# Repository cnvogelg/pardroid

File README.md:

The parbox project implements an external device attached to the
Amiga parallel port that allows to directly connect network or mass
storage devices.

Currently, devices based on Atmel's AVR8 controllers are supported on the
device side.

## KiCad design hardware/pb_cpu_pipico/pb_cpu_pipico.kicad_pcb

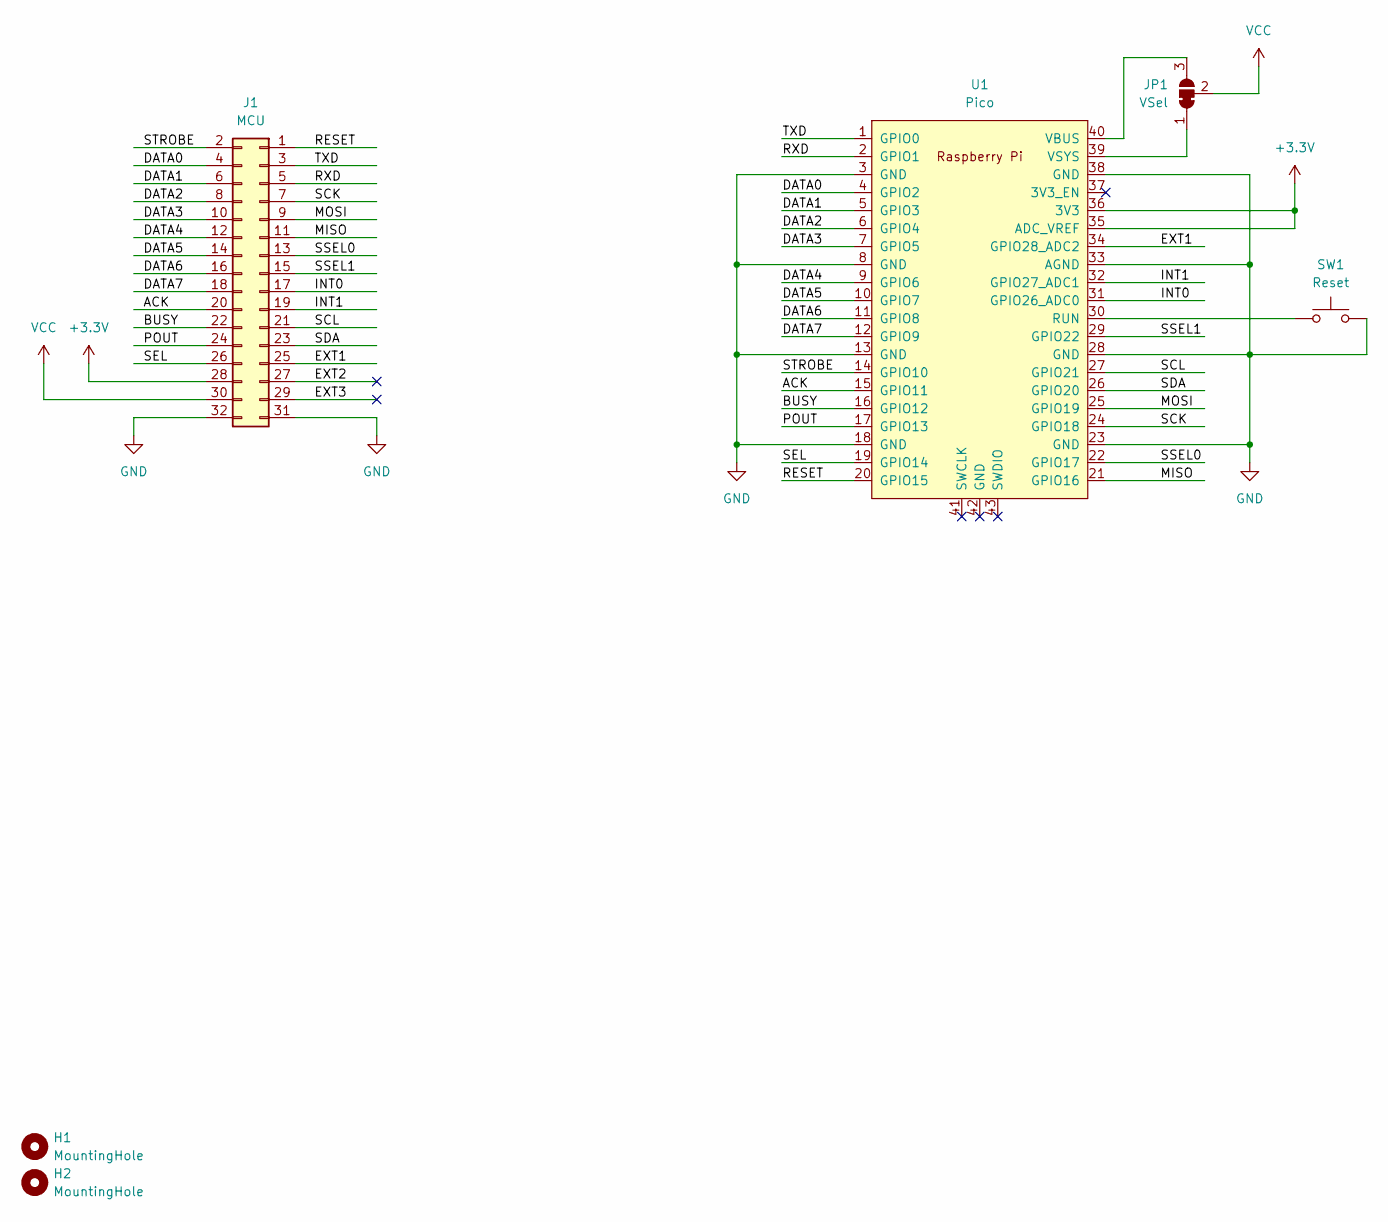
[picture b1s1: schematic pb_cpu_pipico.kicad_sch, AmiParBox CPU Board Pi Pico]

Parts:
H1, H2: MountingHole; MountingHole_3.2mm_M3_Pad
J1: MCU; PinHeader_2x16_P2.54mm_Vertical
JP1: VSel; SolderJumper-3_P1.3mm_Bridged2Bar12_Pad1.0x1.5mm
SW1: Reset; SW_PUSH_6mm
U1: Pico; RPi_Pico_SMD_TH

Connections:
+3V3: J1.28, U1.35 (ADC_VREF), U1.36 (3V3)
/ACK: J1.20, U1.15 (GPIO11)
/BUSY: J1.22, U1.16 (GPIO12)
/DATA0: J1.4, U1.4 (GPIO2)
/DATA1: J1.6, U1.5 (GPIO3)
/DATA2: J1.8, U1.6 (GPIO4)
/DATA3: J1.10, U1.7 (GPIO5)
/DATA4: J1.12, U1.9 (GPIO6)
/DATA5: J1.14, U1.10 (GPIO7)
/DATA6: J1.16, U1.11 (GPIO8)
/DATA7: J1.18, U1.12 (GPIO9)
/EXT1: J1.25, U1.34 (GPIO28_ADC2)
/EXT2: J1.27
/EXT3: J1.29
/INT0: J1.17, U1.31 (GPIO26_ADC0)
/INT1: J1.19, U1.32 (GPIO27_ADC1)
/MISO: J1.11, U1.21 (GPIO16)
/MOSI: J1.9, U1.25 (GPIO19)
/POUT: J1.24, U1.17 (GPIO13)
/RESET: J1.1, U1.20 (GPIO15)
/RXD: J1.5, U1.2 (GPIO1)
/SCK: J1.7, U1.24 (GPIO18)
/SCL: J1.21, U1.27 (GPIO21)
/SDA: J1.23, U1.26 (GPIO20)
/SEL: J1.26, U1.19 (GPIO14)
/SSEL0: J1.13, U1.22 (GPIO17)
/SSEL1: J1.15, U1.29 (GPIO22)
/STROBE: J1.2, U1.14 (GPIO10)
/TXD: J1.3, U1.1 (GPIO0)
GND: J1.31, J1.32, SW1.2, U1.3 (GND), U1.8 (GND), U1.13 (GND), U1.18 (GND), U1.23 (GND), U1.28 (GND), U1.33 (AGND), U1.38 (GND)
unnamed: JP1.1 (A), U1.39 (VSYS)
unnamed: JP1.3 (B), U1.40 (VBUS)
unnamed: SW1.1, U1.30 (RUN)
VCC: J1.30, JP1.2 (C)

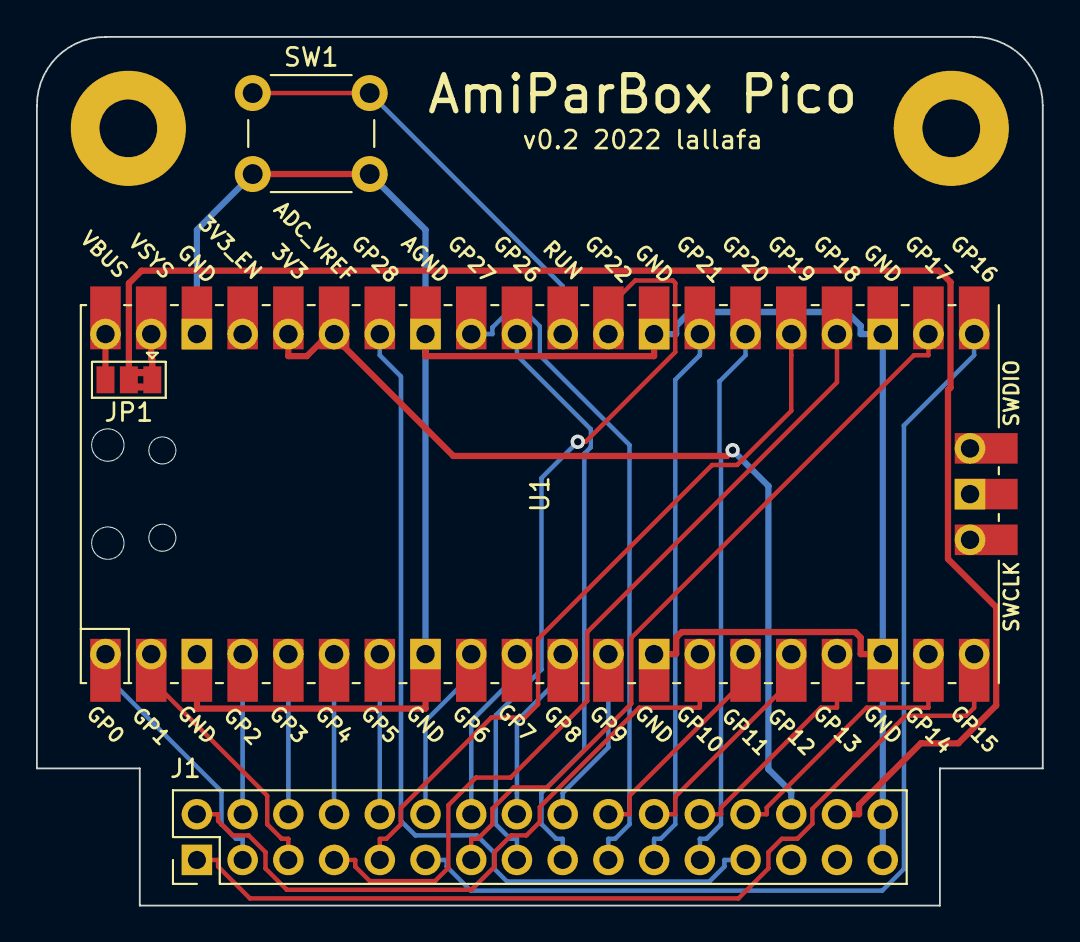
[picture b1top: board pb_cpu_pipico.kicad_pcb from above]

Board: 2 copper layers, 55.9 x 48.3 mm, 6 parts (0 on the bottom side), 32 nets.

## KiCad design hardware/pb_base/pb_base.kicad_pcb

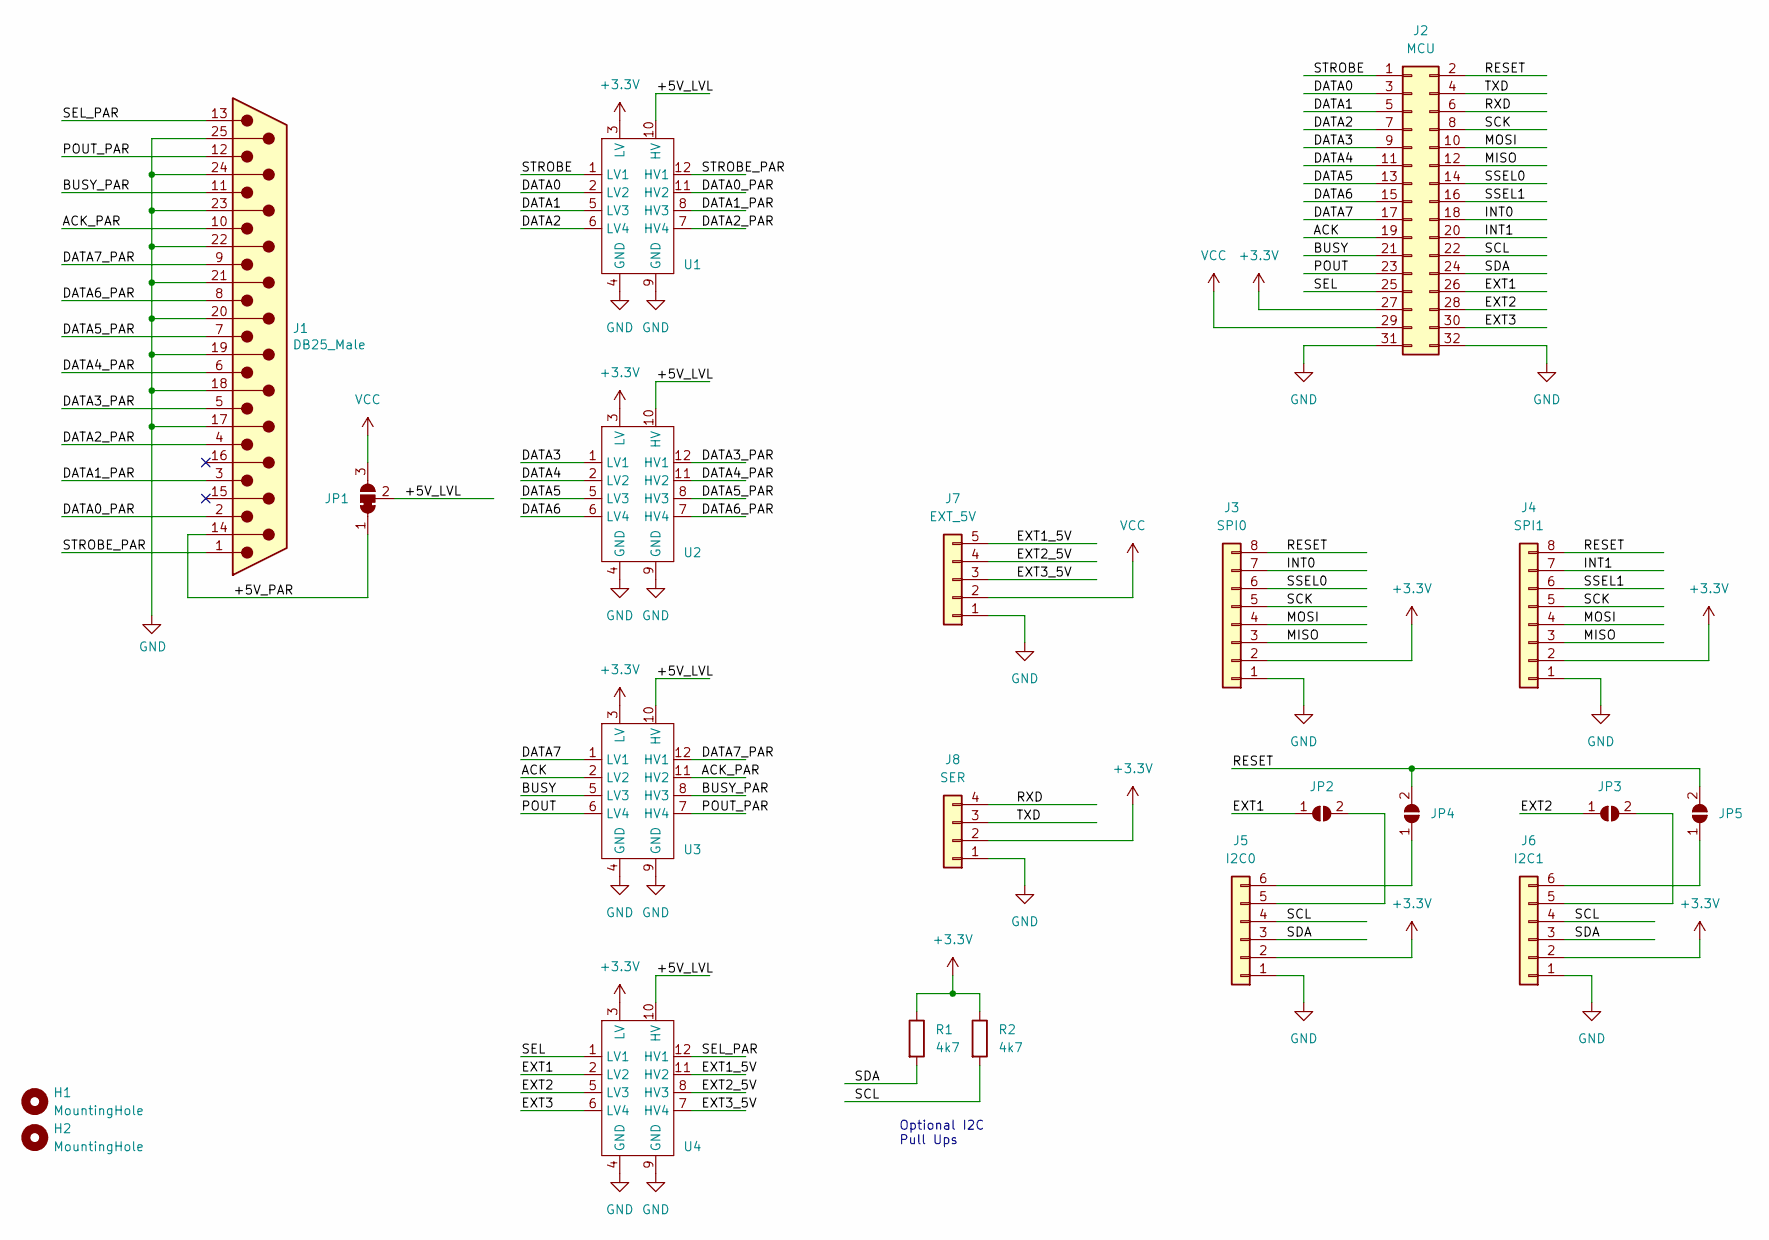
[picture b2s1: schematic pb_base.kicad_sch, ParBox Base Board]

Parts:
H1, H2: MountingHole; MountingHole_3.2mm_M3_Pad
J1: DB25_Male; DSUB-25_Male_Horizontal_P2.77x2.84mm_EdgePinOffset7.70mm_Ho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
J2: MCU; PinHeader_2x16_P2.54mm_Vertical
J3: SPI0; PinHeader_1x08_P2.54mm_Vertical
J4: SPI1; PinHeader_1x08_P2.54mm_Vertical
J5: I2C0; PinHeader_1x06_P2.54mm_Vertical
J6: I2C1; PinHeader_1x06_P2.54mm_Vertical
J7: EXT_5V; PinHeader_1x05_P2.54mm_Vertical
J8: SER; PinHeader_1x04_P2.54mm_Vertical
JP1: SolderJumper_3_Bridged12; PinHeader_1x03_P2.54mm_Vertical
JP2, JP3, JP4, JP5: SolderJumper_2_Open; PinHeader_1x02_P2.54mm_Vertical
R1, R2: 4k7; R_Axial_DIN0204_L3.6mm_D1.6mm_P5.08mm_Horizontal
U1, U2, U3, U4: LevelShifter_4; DIP-12_W10.16mm_LongPads

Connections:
+3V3: J2.27, J3.2, J4.2, J5.2, J6.2, J8.2, R1.1, R2.1, U1.3 (LV), U2.3 (LV), U3.3 (LV), U4.3 (LV)
/+5V_LVL: JP1.2 (C), U1.10 (HV), U2.10 (HV), U3.10 (HV), U4.10 (HV)
/+5V_PAR: J1.14, JP1.1 (A)
/ACK: J2.19, U3.2 (LV2)
/ACK_PAR: J1.10, U3.11 (HV2)
/BUSY: J2.21, U3.5 (LV3)
/BUSY_PAR: J1.11, U3.8 (HV3)
/DATA0: J2.3, U1.2 (LV2)
/DATA0_PAR: J1.2, U1.11 (HV2)
/DATA1: J2.5, U1.5 (LV3)
/DATA1_PAR: J1.3, U1.8 (HV3)
/DATA2: J2.7, U1.6 (LV4)
/DATA2_PAR: J1.4, U1.7 (HV4)
/DATA3: J2.9, U2.1 (LV1)
/DATA3_PAR: J1.5, U2.12 (HV1)
/DATA4: J2.11, U2.2 (LV2)
/DATA4_PAR: J1.6, U2.11 (HV2)
/DATA5: J2.13, U2.5 (LV3)
/DATA5_PAR: J1.7, U2.8 (HV3)
/DATA6: J2.15, U2.6 (LV4)
/DATA6_PAR: J1.8, U2.7 (HV4)
/DATA7: J2.17, U3.1 (LV1)
/DATA7_PAR: J1.9, U3.12 (HV1)
/EXT1: J2.26, JP2.1 (A), U4.2 (LV2)
/EXT1_5V: J7.5, U4.11 (HV2)
/EXT2: J2.28, JP3.1 (A), U4.5 (LV3)
/EXT2_5V: J7.4, U4.8 (HV3)
/EXT3: J2.30, U4.6 (LV4)
/EXT3_5V: J7.3, U4.7 (HV4)
/INT0: J2.18, J3.7
/INT1: J2.20, J4.7
/MISO: J2.12, J3.3, J4.3
/MOSI: J2.10, J3.4, J4.4
/POUT: J2.23, U3.6 (LV4)
/POUT_PAR: J1.12, U3.7 (HV4)
/RESET: J2.2, J3.8, J4.8, JP4.2 (B), JP5.2 (B)
/RXD: J2.6, J8.4
/SCK: J2.8, J3.5, J4.5
/SCL: J2.22, J5.4, J6.4, R2.2
/SDA: J2.24, J5.3, J6.3, R1.2
/SEL: J2.25, U4.1 (LV1)
/SEL_PAR: J1.13, U4.12 (HV1)
/SSEL0: J2.14, J3.6
/SSEL1: J2.16, J4.6
/STROBE: J2.1, U1.1 (LV1)
/STROBE_PAR: J1.1, U1.12 (HV1)
/TXD: J2.4, J8.3
GND: J1.17, J1.18, J1.19, J1.20, J1.21, J1.22, J1.23, J1.24, J1.25, J2.31, J2.32, J3.1, J4.1, J5.1, J6.1, J7.1, J8.1, U1.4 (GND), U1.9 (GND), U2.4 (GND), U2.9 (GND), U3.4 (GND), U3.9 (GND), U4.4 (GND), U4.9 (GND)
unnamed: J5.5, JP2.2 (B)
unnamed: J5.6, JP4.1 (A)
unnamed: J6.5, JP3.2 (B)
unnamed: J6.6, JP5.1 (A)
VCC: J2.29, J7.2, JP1.3 (B)

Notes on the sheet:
Optional I2C Pull Ups

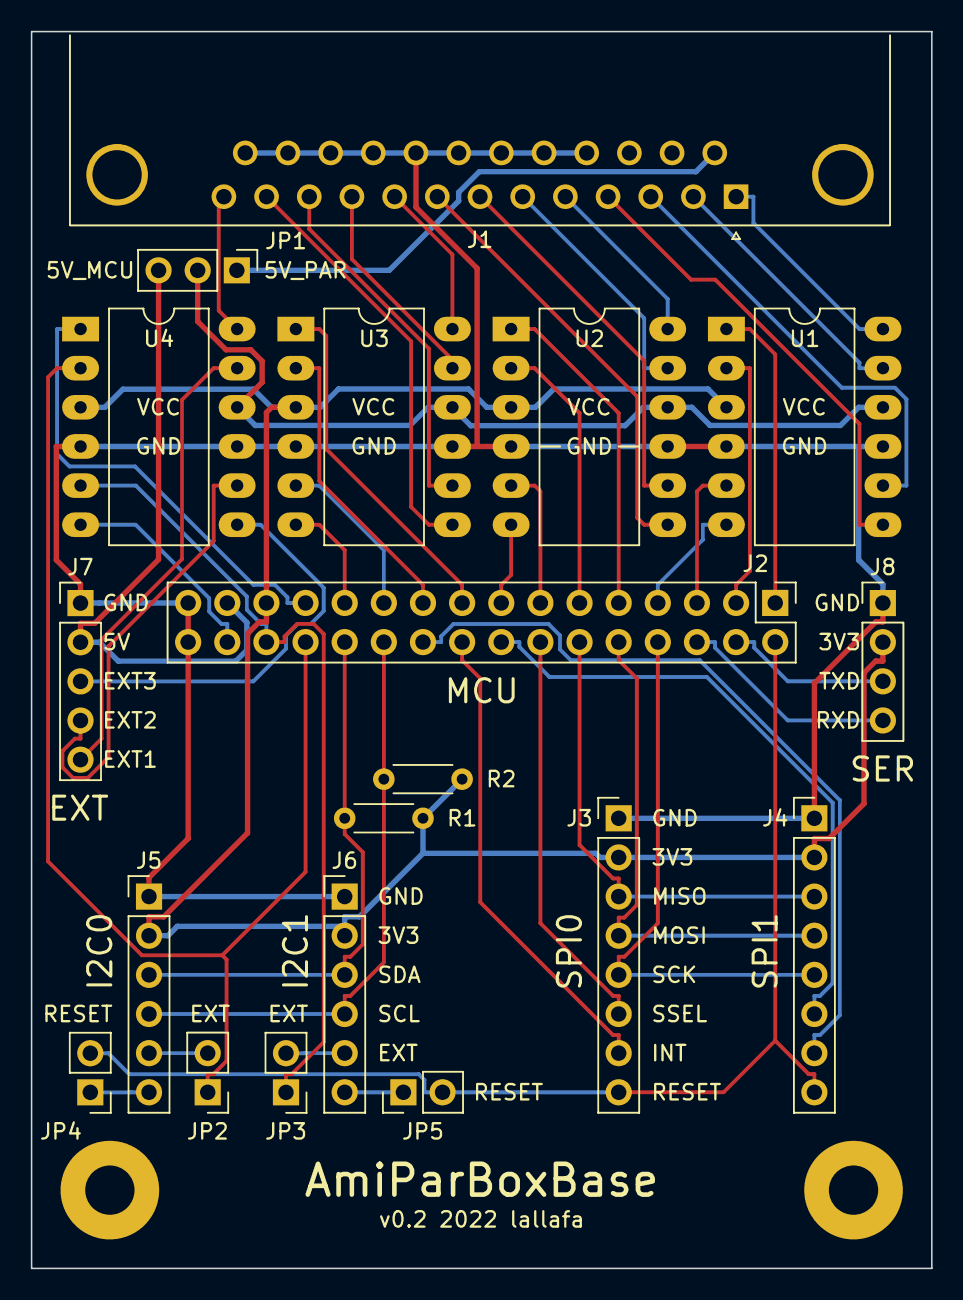
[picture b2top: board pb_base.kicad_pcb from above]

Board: 2 copper layers, 58.4 x 80.3 mm, 21 parts (0 on the bottom side), 53 nets.

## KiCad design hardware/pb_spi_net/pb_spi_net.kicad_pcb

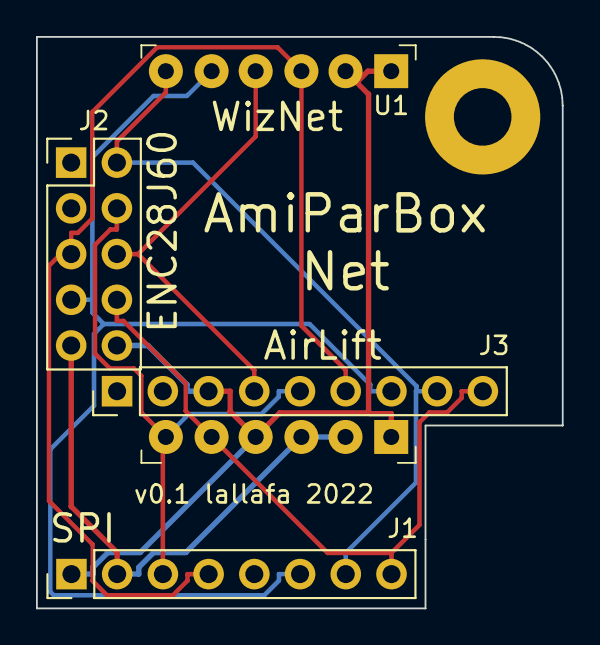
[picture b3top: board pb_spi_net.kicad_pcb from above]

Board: 2 copper layers, 29.2 x 31.8 mm, 5 parts (0 on the bottom side), 8 nets.

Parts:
H1: MountingHole; MountingHole_3.2mm_M3_Pad
J1: SPI; PinHeader_1x08_P2.54mm_Vertical
J2: ENC28J60 Module; PinHeader_2x05_P2.54mm_Vertical
J3: AirLift; PinHeader_1x09_P2.54mm_Vertical
U1: WIZ820IO; Mag_Jack_Module_WIZ820IO

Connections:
+3V3: J1.2, J2.9, U1.J2-2 (3V3D), U1.J2-3 (3V3D)
/INT: J1.7, J2.2, J3.8, U1.J1-6 (nINT)
/MISO: J1.3, J2.4, J3.5, U1.J2-6 (MISO)
/MOSI: J1.4, J2.5, J3.6, U1.J1-3 (MOSI)
/RESET: J1.8, J2.8, J3.9, U1.J2-5 (nRESET)
/SCLK: J2.6, J3.4, U1.J1-4 (SCLK)
/SSEL: J1.6, J2.7, J3.7, U1.J1-5 (nSS)
GND: J1.1, J2.10, J3.3, U1.J1-1 (GND), U1.J1-2 (GND), U1.J2-1 (GND), U1.J2-4 (PWDN)

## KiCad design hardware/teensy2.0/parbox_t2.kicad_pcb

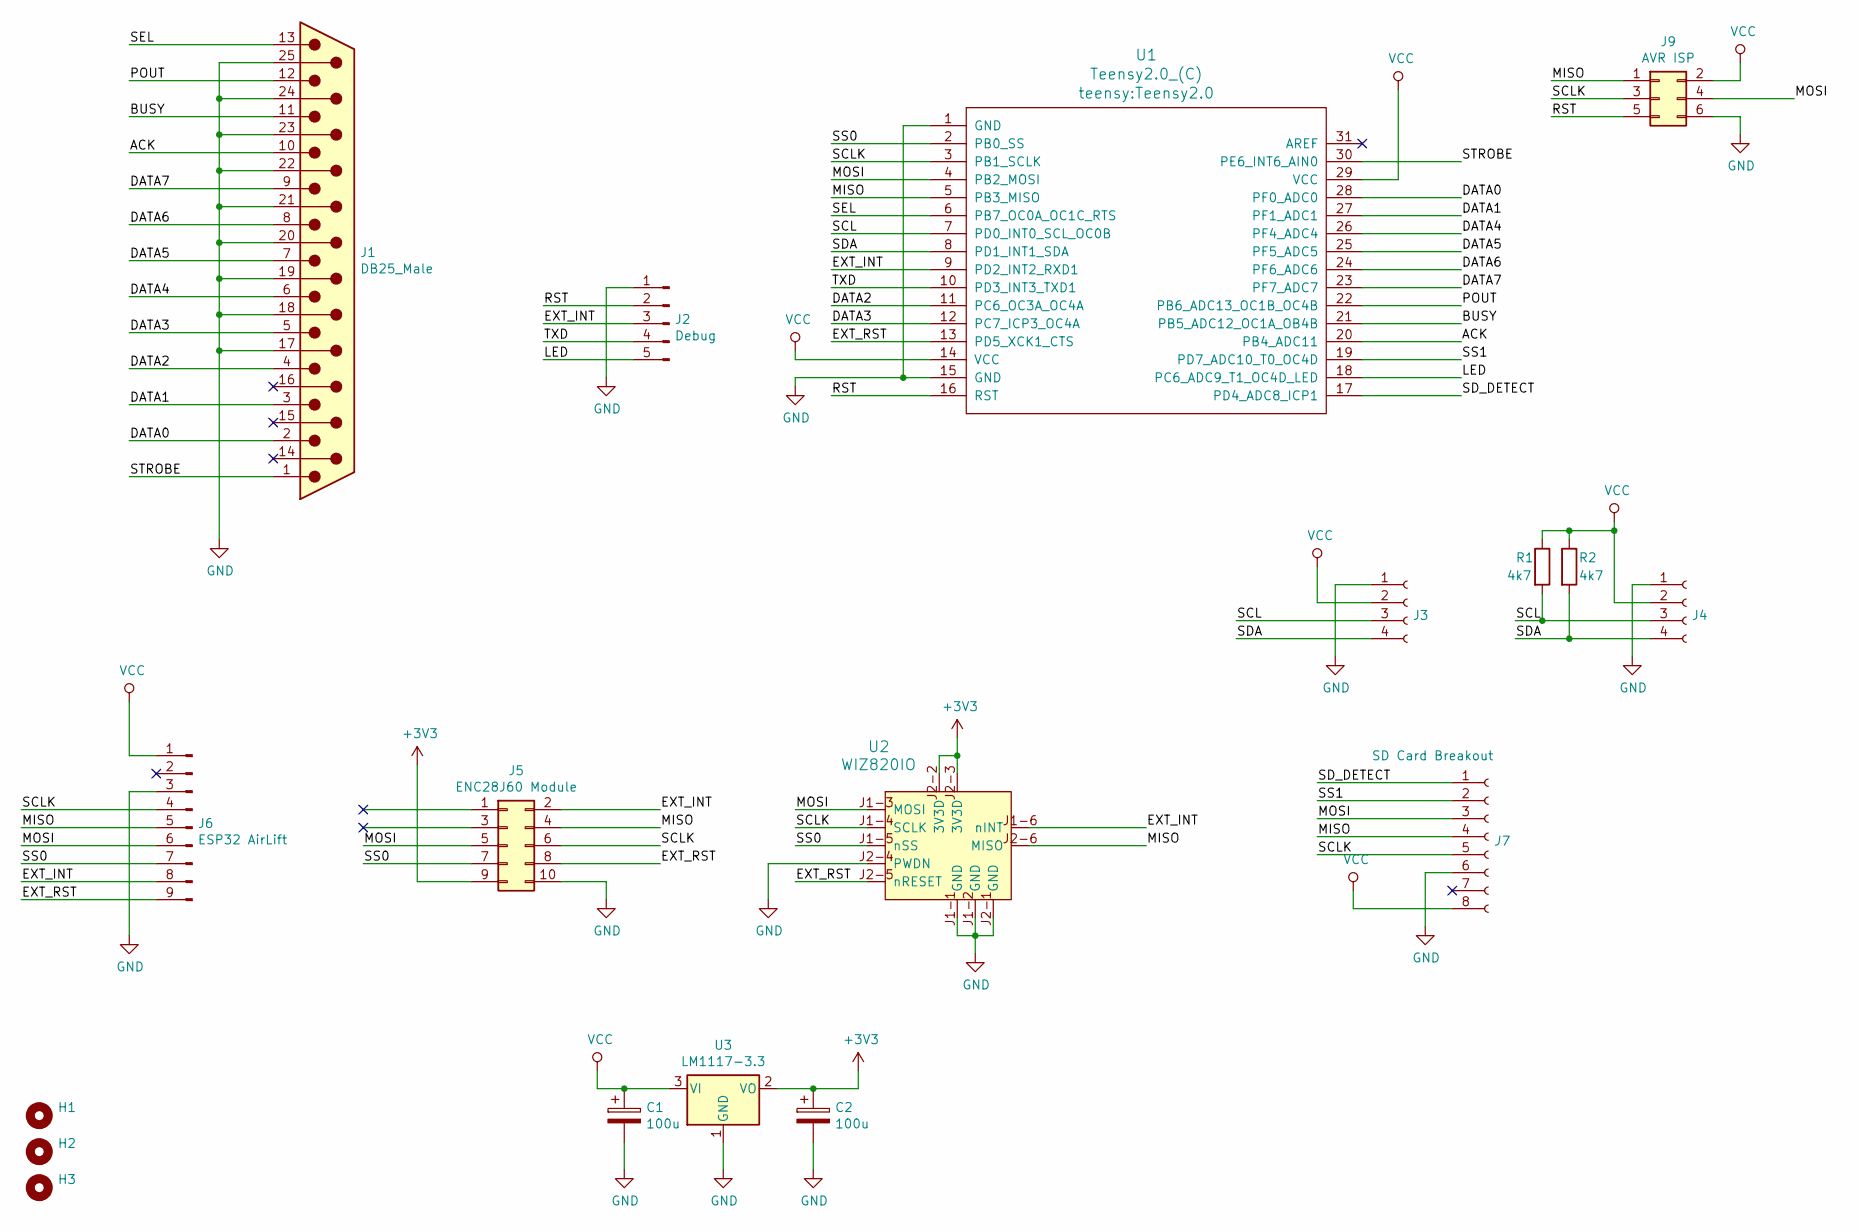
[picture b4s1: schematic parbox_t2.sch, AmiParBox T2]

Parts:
C1, C2: 100u; C_1210_3225Metric_Pad1.42x2.65mm_HandSolder
H1, H2, H3: MountingHole; MountingHole_2.7mm_M2.5_ISO14580_Pad
J1: DB25_Male; DSUB-25_Male_EdgeMount_P2.77mm
J2: Debug; PinHeader_1x05_P2.54mm_Vertical
J3: I2C OLED; PinHeader_1x04_P2.54mm_Vertical
J4: I2C Extra; PinHeader_1x04_P2.54mm_Vertical
J5: ENC28J60 Module; PinHeader_2x05_P2.54mm_Vertical
J6: ESP32 AirLift; PinHeader_1x09_P2.54mm_Vertical
J7: SD Card Breakout; PinHeader_1x08_P2.54mm_Vertical
J9: AVR ISP; PinHeader_2x03_P2.54mm_Vertical
R1, R2: 4k7; R_0805_2012Metric_Pad1.15x1.40mm_HandSolder
U1: Teensy2.0_(C); Teensy2.0
U2: WIZ820IO; Mag_Jack_Module_WIZ820IO; MPN WIZ820IO; Digi-Key_PN 1278-1015-ND
U3: LM1117-3.3; SOT-223-3_TabPin2

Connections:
+3V3: C2.1, J5.9, U2.J2-2 (3V3D), U2.J2-3 (3V3D), U3.2 (VO)
/ACK: J1.10, U1.20 (PB4_ADC11)
/BUSY: J1.11, U1.21 (PB5_ADC12_OC1A_OB4B)
/DATA0: J1.2, U1.28 (PF0_ADC0)
/DATA1: J1.3, U1.27 (PF1_ADC1)
/DATA2: J1.4, U1.11 (PC6_OC3A_OC4A)
/DATA3: J1.5, U1.12 (PC7_ICP3_OC4A)
/DATA4: J1.6, U1.26 (PF4_ADC4)
/DATA5: J1.7, U1.25 (PF5_ADC5)
/DATA6: J1.8, U1.24 (PF6_ADC6)
/DATA7: J1.9, U1.23 (PF7_ADC7)
/EXT_INT: J2.3, J5.2, J6.8, U1.9 (PD2_INT2_RXD1), U2.J1-6 (nINT)
/EXT_RST: J5.8, J6.9, U1.13 (PD5_XCK1_CTS), U2.J2-5 (nRESET)
/LED: J2.5, U1.18 (PC6_ADC9_T1_OC4D_LED)
/MISO: J5.4, J6.5, J7.4, J9.1, U1.5 (PB3_MISO), U2.J2-6 (MISO)
/MOSI: J5.5, J6.6, J7.3, J9.4, U1.4 (PB2_MOSI), U2.J1-3 (MOSI)
/POUT: J1.12, U1.22 (PB6_ADC13_OC1B_OC4B)
/RST: J2.2, J9.5, U1.16 (RST)
/SCL: J3.3, J4.3, R1.2, U1.7 (PD0_INT0_SCL_OC0B)
/SCLK: J5.6, J6.4, J7.5, J9.3, U1.3 (PB1_SCLK), U2.J1-4 (SCLK)
/SDA: J3.4, J4.4, R2.2, U1.8 (PD1_INT1_SDA)
/SD_DETECT: J7.1, U1.17 (PD4_ADC8_ICP1)
/SEL: J1.13, U1.6 (PB7_OC0A_OC1C_RTS)
/SS0: J5.7, J6.7, U1.2 (PB0_SS), U2.J1-5 (nSS)
/SS1: J7.2, U1.19 (PD7_ADC10_T0_OC4D)
/STROBE: J1.1, U1.30 (PE6_INT6_AIN0)
/TXD: J2.4, U1.10 (PD3_INT3_TXD1)
GND: C1.2, C2.2, J1.17, J1.18, J1.19, J1.20, J1.21, J1.22, J1.23, J1.24, J1.25, J2.1, J3.1, J4.1, J5.10, J6.3, J7.6, J9.6, U1.1 (GND), U1.15 (GND), U2.J1-1 (GND), U2.J1-2 (GND), U2.J2-1 (GND), U2.J2-4 (PWDN), U3.1 (GND)
VCC: C1.1, J3.2, J4.2, J6.1, J7.8, J9.2, R1.1, R2.1, U1.14 (VCC), U1.29 (VCC), U3.3 (VI)

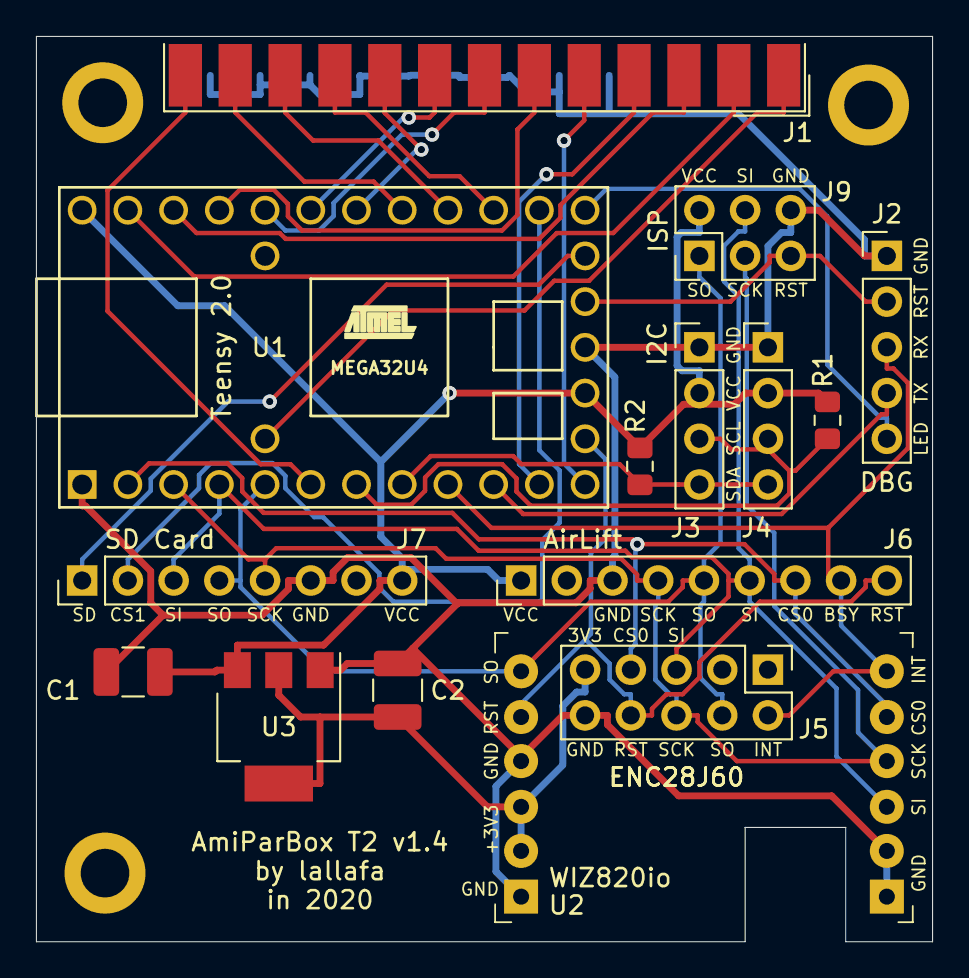
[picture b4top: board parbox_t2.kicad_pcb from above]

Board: 2 copper layers, 49.8 x 50.3 mm, 18 parts (0 on the bottom side), 29 nets.

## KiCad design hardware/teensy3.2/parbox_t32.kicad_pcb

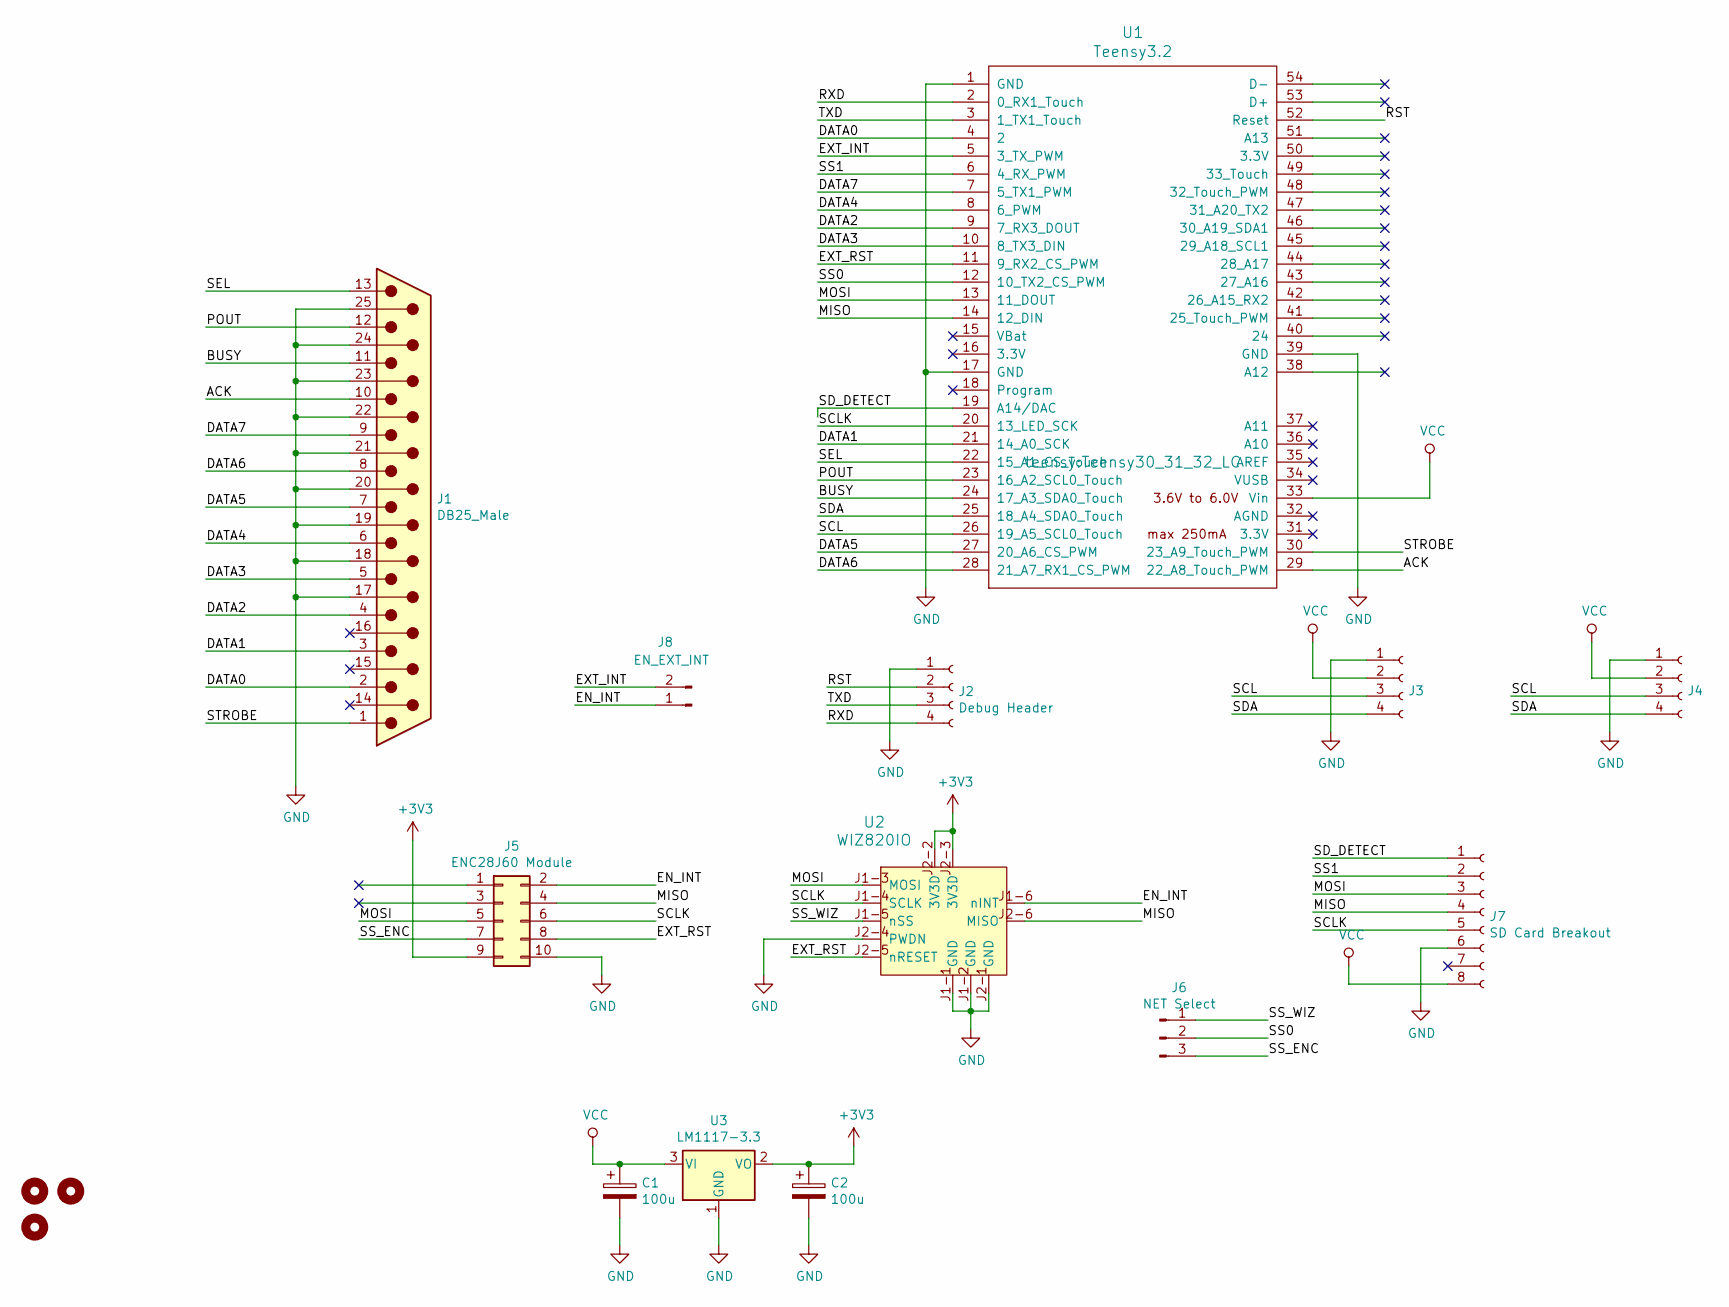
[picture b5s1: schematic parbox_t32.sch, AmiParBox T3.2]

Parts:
C1, C2: 100u; C_1210_3225Metric_Pad1.42x2.65mm_HandSolder
H1, H2, H3: MountingHole; MountingHole_2.7mm_M2.5_Pad
J1: DB25_Male; DSUB-25_Female_EdgeMount_P2.77mm
J2: Debug Header; PinHeader_1x04_P2.54mm_Vertical
J3: I2C OLED; PinHeader_1x04_P2.54mm_Vertical
J4: I2C Extra; PinHeader_1x04_P2.54mm_Vertical
J5: ENC28J60 Module; PinHeader_2x05_P2.54mm_Vertical
J6: NET Select; SolderJumper-3_P1.3mm_Open_RoundedPad1.0x1.5mm_NumberLabels
J7: SD Card Breakout; PinHeader_1x08_P2.54mm_Vertical
J8: EN_EXT_INT; SolderJumper-2_P1.3mm_Bridged_RoundedPad1.0x1.5mm
U1: Teensy3.2; Teensy30_31_32_LC
U2: WIZ820IO; Mag_Jack_Module_WIZ820IO; MPN WIZ820IO; Digi-Key_PN 1278-1015-ND
U3: LM1117-3.3; SOT-223-3_TabPin2

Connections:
+3V3: C2.1, J5.9, U2.J2-2 (3V3D), U2.J2-3 (3V3D), U3.2 (VO)
/ACK: J1.10, U1.29 (22_A8_Touch_PWM)
/BUSY: J1.11, U1.24 (17_A3_SDA0_Touch)
/DATA0: J1.2, U1.4 (2)
/DATA1: J1.3, U1.21 (14_A0_SCK)
/DATA2: J1.4, U1.9 (7_RX3_DOUT)
/DATA3: J1.5, U1.10 (8_TX3_DIN)
/DATA4: J1.6, U1.8 (6_PWM)
/DATA5: J1.7, U1.27 (20_A6_CS_PWM)
/DATA6: J1.8, U1.28 (21_A7_RX1_CS_PWM)
/DATA7: J1.9, U1.7 (5_TX1_PWM)
/EN_INT: J5.2, J8.1, U2.J1-6 (nINT)
/EXT_INT: J8.2, U1.5 (3_TX_PWM)
/EXT_RST: J5.8, U1.11 (9_RX2_CS_PWM), U2.J2-5 (nRESET)
/MISO: J5.4, J7.4, U1.14 (12_DIN), U2.J2-6 (MISO)
/MOSI: J5.5, J7.3, U1.13 (11_DOUT), U2.J1-3 (MOSI)
/POUT: J1.12, U1.23 (16_A2_SCL0_Touch)
/RST: J2.2, U1.52 (Reset)
/RXD: J2.4, U1.2 (0_RX1_Touch)
/SCL: J3.3, J4.3, U1.26 (19_A5_SCL0_Touch)
/SCLK: J5.6, J7.5, U1.20 (13_LED_SCK), U2.J1-4 (SCLK)
/SDA: J3.4, J4.4, U1.25 (18_A4_SDA0_Touch)
/SD_DETECT: J7.1, U1.19 (A14/DAC)
/SEL: J1.13, U1.22 (15_A1_CS_Touch)
/SS0: J6.2, U1.12 (10_TX2_CS_PWM)
/SS1: J7.2, U1.6 (4_RX_PWM)
/SS_ENC: J5.7, J6.3
/SS_WIZ: J6.1, U2.J1-5 (nSS)
/STROBE: J1.1, U1.30 (23_A9_Touch_PWM)
/TXD: J2.3, U1.3 (1_TX1_Touch)
GND: C1.2, C2.2, J1.17, J1.18, J1.19, J1.20, J1.21, J1.22, J1.23, J1.24, J1.25, J2.1, J3.1, J4.1, J5.10, J7.6, U1.1 (GND), U1.17 (GND), U1.39 (GND), U2.J1-1 (GND), U2.J1-2 (GND), U2.J2-1 (GND), U2.J2-4 (PWDN), U3.1 (GND)
VCC: C1.1, J3.2, J4.2, J7.8, U1.33 (Vin), U3.3 (VI)

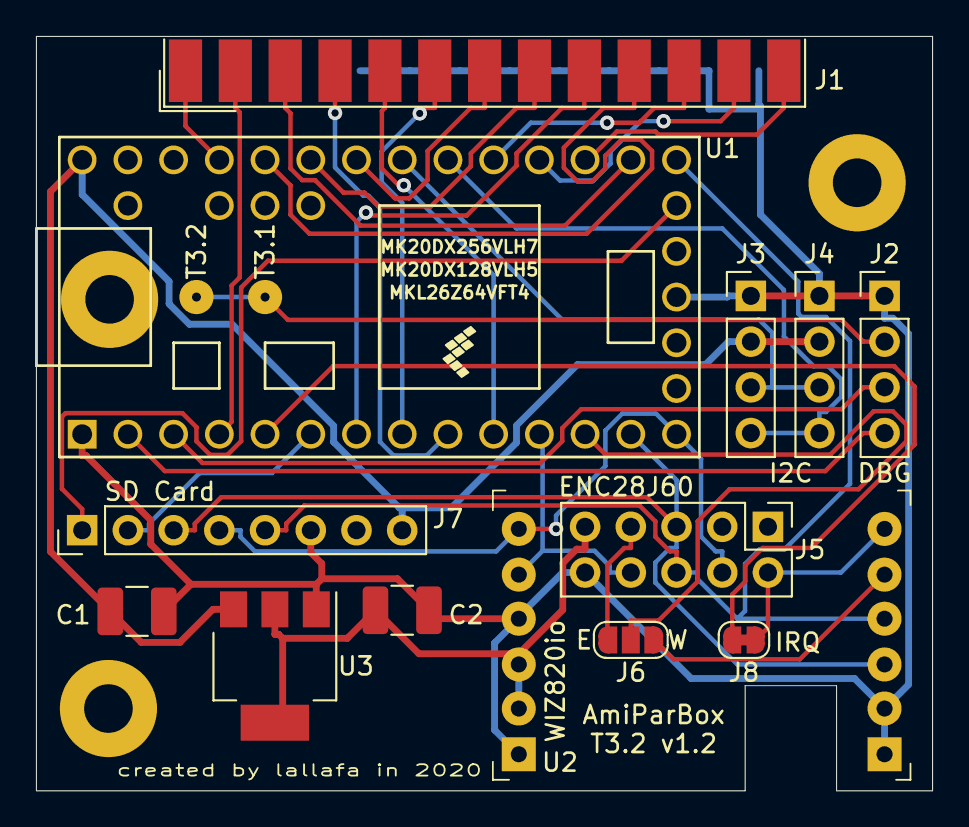
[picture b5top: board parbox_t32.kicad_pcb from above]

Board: 2 copper layers, 49.8 x 41.9 mm, 16 parts (0 on the bottom side), 32 nets.

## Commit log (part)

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2017-03-19 first flash
2017-03-19 added verify
2017-03-28 added mcu dist
2017-03-28 system.c is an avr file
2017-03-28 added multi config support
2017-03-28 machtag handling moved to Python
2017-03-28 split up config
2017-03-28 added avrnetio board
2017-03-28 added teensy20 board
2017-03-29 cleanup avrdude rules
2017-03-29 added pbnano fuses
2017-03-30 improved reg_ro
2017-03-30 stared handling of pending requests
2017-03-30 added ro reg defaults
2017-03-30 reg_ro cleanup
2017-03-31 added reg_rw
2017-03-31 run all tests
2017-03-31 fixes
2017-04-04 refactored tests
2017-04-04 removed obsolete tests
2017-04-04 fixed test runner
2017-04-09 added time calc funcs
2017-04-09 added signal based timer
2017-04-11 renamed proto_action
2017-04-11 added bench actions
2017-04-13 add pending read
2017-04-17 cleanup reg_rw
2017-04-17 refactored actions
2017-04-18 fixed pending flag
2017-04-19 fixed bench callback
2017-04-23 check for config
2017-04-23 cleanup eclock calc
2017-04-23 added ack test
2017-04-25 added handler
2017-04-29 disable pin debug by default
2017-04-29 cleanup dist rules
2017-05-05 added amiga dist
2017-05-05 added dist makefile
2017-05-07 teensy20 fixes
2017-05-07 fixed teensy20 pin doc
2017-05-07 fix mach define
2017-05-07 teensy20 requires ISP
2017-05-10 added master makefile
2017-05-10 added worker
2017-05-10 added main makefile
2017-05-19 added amiga reg access
2017-05-19 started engine
2017-05-21 added channel and request
2017-05-24 engine write
2017-05-25 started engine client
2017-05-30 abort write if read is pending
2017-05-30 recv msg: added channel + extra
2017-06-06 send with channel
2017-06-06 unified regs
2017-06-10 fixed test
2017-06-11 use ddr for write, too
2017-06-11 new reg commands
2017-06-13 switch to cmd bits in idle byte
2017-06-13 rewrote functions and register access
2017-06-14 fixed rom wptr
2017-06-14 ignore invalid
2017-06-16 introducing status bits
2017-06-16 unify pending and status
2017-06-16 new status handling
2017-06-16 added missing files
2017-06-17 added func table
2017-06-17 shrunk reg table
2017-06-17 use 4/4 idle byte split
2017-06-20 status fixes
2017-06-21 fixed bootloader
2017-10-20 added echo handler
2017-10-22 fixed handler
2017-10-25 function cleanup
2017-10-25 added offset support
2017-10-26 allow to abort write msg on slave side
2017-10-26 fixed error message
2017-10-26 abort read if message is too large
2017-10-26 remove low level debug
2017-10-26 read end status added
2017-10-26 finer debug control
2017-10-26 buffer fixes
2017-10-30 allow reg ranges
2017-10-31 added driver
2017-10-31 handler regs defined
2017-10-31 simplified handler read/write
2017-10-31 refactored proto dir
2017-11-07 created multiple test firmwares
2017-11-07 added fw_id to pablo
2017-11-08 started teensy32 port
2017-11-13 own header for regs
2017-11-13 more msg tests
2017-11-14 mk20 sys support
2017-11-14 mk20: fix watchdog
2017-11-14 mk20: started gpio
2017-11-14 mk20: proto low
2017-11-14 force inline pario code
2017-11-15 mk20: fixed read block
2017-11-15 mk20: fix reset
2017-11-16 cleanup status handling
2017-11-16 restructured amiga tests
2017-11-16 started bench tool
2017-11-16 optimized clk in main loop
2017-11-16 cleaned up status handling
2017-11-17 started enc28j60 driver
2017-11-19 started sdcard
2017-11-20 sd init
2017-11-20 sd: get capacity
2017-11-21 sd: added read/write
2017-11-21 sd: added crc checks
2017-11-21 avr: disable irq in critical proto sections
2017-11-22 added knok seq at start
2017-11-22 handle reset with knok exit
2017-11-24 mk20: added spi
2017-11-30 new teensy20 parallel pinout
2017-12-01 started wiznet driver
2017-12-03 more wiz io
2017-12-06 wiz udp sent
2017-12-07 udp recv
2017-12-08 udp partial recv/send
2017-12-08 added wiz eth mode
2017-12-11 enc28j60 test added
2017-12-12 driver rework
2017-12-13 driver rewrite
2017-12-15 added param handling
2017-12-16 added test-param
2017-12-16 added eeprom support for teensy3
2017-12-16 param fixes
2017-12-22 added bootstrap
2017-12-23 started rexx based bootstrap
2017-12-23 use leds for knok
2017-12-25 boot.rexx with crc check
2017-12-25 smaller boot.rexx
2017-12-26 introduced pamela
2017-12-26 mcu pamela renaming
2017-12-26 make bootstrap optional
2017-12-26 mk20: added strobe
2017-12-27 proto iov rework
2017-12-29 fixed extra word in test-pamela. fixed bootloader size
2017-12-29 fixed knok exit
2017-12-29 fixed boot.rexx
2017-12-29 boot.rexx: use faster word check sum
2017-12-29 k20: fixed strobe
2017-12-29 fix bench naming
2017-12-29 renamed offset to long reg
2018-01-03 started ufat driver
2018-01-04 ufat file read
2018-01-06 added ufat blk io
2018-01-09 heap based alloc
2018-01-09 added stack pointer check
2018-01-10 restructed files
2018-01-10 introduced pamela funcs
2018-01-10 paloma structure
2018-01-10 add channel map
2018-01-12 renamed error flag to event_mask
2018-01-12 allow to replace msg io
2018-01-12 started amiga paloma
2018-01-19 reworked pamela Amiga API
2018-01-20 fixed dist and fixed bootloader
2018-01-20 disable dist tag
2018-01-20 amiga dist: added boot.run sfx lha
2018-01-23 mcu dist rules reworked
2018-01-23 mcu: trigger irq after command
2018-01-23 clear event mask on read
2018-01-24 event signal fixes
2018-01-25 fixed signal tests
2018-01-25 added pending mask handling
2018-01-26 simplified knok exit
2018-01-28 fixed pablo
2018-01-28 improved tests
2018-01-28 set channel in event
2018-01-28 added test for irq after reset
2018-01-28 rework read pending
2018-01-28 more pending tests
2018-01-28 test event while pending
2018-01-29 added mwr+sig bench
2018-01-29 echo test mode
2018-01-29 no bootstrap
2018-01-29 more status debug
2018-01-29 proto: set status correctly after msg read/write
2018-01-29 fix bench
2018-01-29 proto cleanup
2018-01-29 improved pb-bench
2018-01-30 reworked detach signal
2018-01-30 added busy. fixed write too large sync
2018-01-30 simplified status handler
2018-01-31 added flavor support
2019-01-24 fixed inlining
2019-01-24 fixed install
2019-03-14 vc build fixes
2019-03-28 use sphinx for docs
2019-04-01 started major proto rewrite
2019-04-02 adapted teensy3 port
2019-04-04 added busy flag
2019-04-04 re-added regs
2019-04-04 fixed reset glitches
2019-04-05 rebuild pamela test
2019-04-05 abort msg cmd if busy
2019-04-05 added event tests
2019-04-16 knok: delay irq init so no ack is generated in exyt
2019-04-16 fixed msg write too large
2019-04-16 added test for read too large
2019-04-16 reset after write fail
2019-04-16 fixed busy test
2019-04-16 m68k asm: improved busy checking
2019-04-16 added busy support for functions and actions
2019-04-16 fixed signal setup
2019-04-18 bootloader supports u32 size and addr
2019-04-18 generalized bootloader
2019-04-18 fixed read too large msg
2019-04-18 added test for trigger after busy
2019-04-18 added rx pending and error test
2019-07-12 split msg transfer into size word and actual data
2019-07-12 removed regs in pamela
2019-07-12 set rx pending after write msg in test
2019-07-19 fixed handling of too large msg writes
2019-07-19 added direct spi msg transfer
2019-07-25 reduced debug bootloader size
2019-07-25 added spi block commands for common
2019-07-25 added enc28j60 ram test
2019-07-27 added enc28j60 test to pamela suite
2019-07-28 fixed spi use after spi msg transfer
2019-07-28 added offsets
2019-07-28 added enc to teensy32
2019-08-01 added MTU support
2019-08-01 fix bootloader page size
2019-08-02 added amiga gcc support
2019-08-02 gcc fixes
2019-08-05 cleaned up func ids
2019-10-10 started pambox.device
2019-10-11 renamed pamela.device
2019-10-11 removed paloma and worker
2019-10-11 correctly renamed pamela.device
2019-10-11 more engine work
2019-10-11 added worker open/close
2019-10-11 removed old engine
2019-10-11 new pamnet device
2019-10-19 added missing file
2019-10-22 gcc fix
2019-10-22 simplified bootloader proto
2019-12-10 proto fw works with new setup again
2019-12-12 converted Amiga build to new proto
2019-12-12 mcu: introduced proto module
2019-12-12 fixed fw info
2019-12-13 fixed tests
2019-12-13 add more ext tests
2019-12-13 added msg spi tests
2019-12-13 fixed proto bench
2019-12-13 return to knok after test/bench
2020-01-06 added teensy 2.0 hardware
2020-01-09 added Teensy 3.2 hardware
2020-01-11 amiga: started channel work
2020-01-22 hw: update t2 rev 1.4
2020-01-30 added initial display ssd1306 support
2020-02-04 proto: read/write block with max_words
2020-02-05 complete channel rewrite on Amiga side
2020-02-06 mcu: adjusted proto cleanup
2020-02-06 removed obsolete output
2020-02-07 added more help
2020-02-07 added test-pamela fw
2020-02-09 fixed proto on Amiga side
2020-02-09 fixed channel open/close
2020-02-15 added mk20 i2c driver
2020-02-15 faster i2c
2020-02-20 added UDP test
2020-02-20 refactored proto_low
2020-02-20 moved mach code
2020-02-20 introduced net mach
2020-04-01 more net udp stuff
2020-04-01 udp msg proto
2021-08-11 fixed alib includes
2021-08-29 use new udp impl
2021-09-17 added sim_pkt
2021-10-15 sim update
2021-10-15 remove iov
2021-10-21 added proto atom
2021-10-22 added env tests
2021-10-22 added test atom fw
2021-10-24 added busy tests
2021-11-08 mcu: added proto-dev
2021-11-08 mcu: simplified dev api
2021-11-20 added rominfo string
2021-11-20 added knok info
2021-11-20 added flavor to rominfo
2021-11-21 mcu proto build cleanup
2021-11-21 rework amiga build
2021-11-21 proto env is now a base of proto atom
2021-11-21 added initial proto dev test suite
2021-11-22 fixed rominfo
2021-11-22 renamed minitests
2021-11-22 fixed proto atom minitest
2021-11-22 fix mini test proto dev
2021-11-22 add more dev tests
2021-12-28 added proto-io
2021-12-30 added proto-boot
2021-12-30 removed old proto
2021-12-30 ported bootloader to new proto-boot
2021-12-30 bootloader fixes
2022-02-11 hw: added new base board and pico
2022-03-01 hw: updated base and pico to 0.2
2022-03-03 initial support for pico
2022-03-03 fixed avr build
2022-03-03 fixed mk20 build
2022-03-04 started new pamela
2022-03-05 fixed pico uart
2022-03-05 pico fixes
2022-03-06 fixed slow pico funcs
2022-03-06 added .editorconfig
2022-03-06 pico strobe fixes
2022-03-09 added mcu pamela
2022-03-10 refactored pamela status
2022-03-22 pamela fixes
2022-03-22 more pamela fixes
2022-03-22 pamela test fixes
2022-03-24 added pamela engine
2022-03-27 added pamela-engine test
2022-04-07 added pamela.device
2022-04-07 added bench-proto-io
2022-04-09 use async open/reset/close
2022-04-15 async open/reset/close in pamela
2022-04-16 fixed test-pamela
2022-04-16 add port param to test-pamela-engine
2022-04-16 refactored stop watch in bench
2022-04-16 added bench-pamela
2022-04-17 more proto-io benches
2022-04-19 fixed sdcard
2022-04-23 re-enabled enc28j60 test
2022-04-23 re-enabled test-wiznet
2022-04-26 fixed enc28j60 test
2022-04-28 re-added test-display
2022-06-13 added pamlib
2022-06-13 add seek/tell test
2022-06-14 added pam-info
2022-06-22 started paloma
2022-06-28 enhanced minitest paloma
2022-06-30 added mcu paloma
2022-07-14 paloma fixes
2022-07-18 refactored common include
2022-08-27 removed attic handler
2022-09-24 added pamlib_req
2022-09-24 added srv id
2022-09-30 added support for odd sized messages in pamela
2022-10-15 added mcu pamela_req
2022-10-15 added amiga pam req
2022-10-16 fixed minitest pamlib_req
2022-10-16 added test-pamlib_req
2022-10-18 added pamlib_req test
2022-10-18 removed watchdog
2022-10-22 added fatfs
2022-10-22 nuked ufat
2022-10-26 pamela uses rom tables now
2022-10-26 added malloc() test
2022-10-26 renamed _work to _poll in pamela
2022-10-27 added pamela_req handle_poll()
2022-10-30 paloma now uses pamela_req
2022-10-30 moved odd size handling to proto_io
2022-11-24 added disk
2022-11-25 added proto_io channel error
2022-11-25 made proto-io test free from pamela deps
2022-11-25 pamela: added open error handling/tests
2022-11-25 added tests for read/write errors
2022-11-25 added error tests to pamela engine
2022-11-25 added missing disk stuff
2022-11-25 close channel on open error
2022-11-25 fix open error test in pamlib
2022-11-25 added r/w error tests in pamlib
2022-11-25 adjusted pamela_req to new done return
2022-12-25 improved mcu pamela API
2023-01-20 prepare multi block read/write
2023-01-20 fix pamela multi block r/w
2023-01-20 multi block r/w for engine
2023-01-20 pamela_read/write_setup returns actual size
